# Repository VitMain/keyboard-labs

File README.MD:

# Keyboard Labs

This repository contains the source files for keyboard
designs and keyboard firmware.

# Keyboards

Kicad source files are in `pcb`.

Plotted gerber files can be found under the GitHub repository's
[releases](https://github.com/rgoulter/keyboard-labs/releases/).

| Designation  | Summary/Keywords                                                                       | Image                                                                                                                                                 |
|--------------|----------------------------------------------------------------------------------------|-------------------------------------------------------------------------------------------------------------------------------------------------------|
| [X-1](https://github.com/rgoulter/keyboard-labs#x-1-36-key-split-reversible-pcb-with-weact-studio-mini-f4-dev-board) | 36-key (2x3x5+3), split, column-staggered, MX/choc, sub-100x100, per-key RGB LED, ARM       |                               |
| [X-2](#x-2-5x12-ortholinear-arm-powered-adaptation-of-peejs-lumberjack-pcb)          | 60-key (5x12), un-split, ortholinear, MX/choc, GH60-compatible, "show the components", ARM  |                               |
| [X-2 HSRGB](#x-2-hsrgb-5x12-ortholinear-arm-powered-adaptation-of-peejs-lumberjack-pcb-with-hotswap-and-per-key-rgb)    | 60-key (5x12), un-split, ortholinear, MX/choc, GH60-compatible, "show the components", HotSwap, per-key RGB, ARM  |    |
| [PyKey40 Lite](#pykey40-lite-no-frills-subset-of-the-pykey60-in-bm40jj40-form-factor) | Planck-MIT (4x12, 1x2U), ortholinear, MX, BM40/JJ40-compatible, PCBA, no frills, ARM        |                                                                                                                                                       |
| [PyKey40 HSRGB](#pykey40-hsrgb-4x12-ortholinear-with-hotswap-and-rgb-in-bm40jj40-form-factor) | Planck-MIT (4x12, 1x2U), ortholinear, MX, BM40/JJ40-compatible, PCBA, HotSwap, per-key RGB LED, ARM        |   |
| [Pico42](#pico42-simple-hand-solderable-pcb-in-bm40jj40-form-factor) | 42-key ortholinear, MX/choc, BM40/JJ40-compatible, no frills, ARM        |  |
| [CH552-44](#ch552-44-low-budget-hand-solderable-pcb-in-bm40jj40-form-factor) | 44-key ortholinear, MX, BM40/JJ40-compatible, no frills        |  |
| [CH552-48](#ch552-48-low-budget-pcba-in-bm40jj40-form-factor) | 48-key ortholinear (4x12), MX, BM40/JJ40-compatible, no frills        |  |
| [CH552-48-LPR](#ch552-48-lpr-low-budget-pcba-with-low-profile-redragon-switches) | 48-key ortholinear (4x12), low profile redragon, no frills        |  |
| [CH552-36](#ch552-36-low-budget-36-key-split-keyboard-with-smt-components) | 36-key (2x3x5+3), split, column-staggered, MX, sub-100x100, no frills        |  |
| [WABBLE-60](#wabble-60-5x12-ortholinear-ble-risc-v-powered-adaptation-of-peejs-lumberjack-pcb) | 60-key (5x12), unsplit, ortholinear, MX, GH60-compatible, "show the components", RISC-V        |  |
| [CH32X-48](#ch32x-48-low-budget-pcba-in-bm40jj40-form-factor) | 48-key ortholinear (4x12), MX, BM40/JJ40-compatible, no frills, Risc-V |  |
| [CH32X-36](#ch32x-36-low-budget-36-key-split-keyboard-with-smt-components) | 36-key (2x3x5+3), split, column-staggered, MX, sub-100x100, no frills, RISC-V        |  |
| [CH32X-75-LPR](#ch32x-75-lpr-low-budget-pcba-with-low-profile-redragon-switches) | 75-key ortholinear (5x15), low profile redragon, no frills, RISC-V        |  |

## X-1: 36-key, split, reversible PCB with WeAct Studio Mini F4 dev board

Design goals:

- PCB smaller than 100x100 mm2, so that it's cheaper to fabricate at various PCB
  fabricators.
- Reversible PCB (use the same PCB for left/right halves).
- Using the WeAct Studio MiniF4 "black pill" dev board, a cheap STM32F4 dev
  board that runs ARM.
- Low profile (PCB + choc switches + bumpons).
- Column-staggered arrangement of key switches.
- Fancy features: e.g. per-key RGB LEDs, rotary encoders, OLED screen, DC vibration motors.

Pictures:

_X-1, rev2021.5, MX variation (with rotary encoder, OLED, etc.)._

_X-1, rev2021.5, Choc variation, low-profile (with flipped GD-32 Bluepill devboards)._

_Height comparison between low-profile build (with Choc switches) and with sandwich-case._

_Tented._

_Showing the underside of the PCB through the acrylic bottom layer._

_2D Renders of the PCB, revision rev2021.5_

### Build Guides

- [rev2021.4 Budget Build Guide](docs/buildguide_rev2021.4_budget.md)

- [rev2021.5 Interactive BOM](https://rgoulter.com/keyboard-labs/ibom-keyboard-100x100-minif4-dual-rgb-reversible-rev2021.5.html)

- [rev2021.5 Interactive BOM, No Frills](https://rgoulter.com/keyboard-labs/ibom-x1-minif4_36-rev2021.5-basic.html)

### Keyboard Layout

- Blank Layout at [keyboard-layout-editor.com](http://www.keyboard-layout-editor.com/##@_name=MiniF4%20%22Black%20Pill%22%2036-key%20Split%20Keyboard&notes=PCB%20available%20at%2F:%20https%2F:%2F%2F%2F%2Fgithub.com%2F%2Frgoulter%2F%2Fkeyboard-labs%2F%2F&pcb:true&css=%23keyboard-bg%20%7B%0A%20%20%20%20background-image%2F:%20url(%22https%2F:%2F%2F%2F%2Fraw.githubusercontent.com%2F%2Frgoulter%2F%2Fkeyboard-labs%2F%2Fmaster%2F%2Fdocs%2F%2Fimages%2F%2Fkeyboard-100x100-minif4-dual-rgb-reversible-rev2021.4-ortho-bare-sm.png%22)%2F%3B%0A%7D%3B&@_x:2&a:7%3B&=&_x:5.5%3B&=%3B&@_y:-0.95&x:3%3B&=&_x:3.5%3B&=%3B&@_y:-0.9500000000000001&x:4%3B&=%3B&@_y:-1&x:1%3B&=&_x:4.5%3B&=&_x:2%3B&=%3B&@_y:-0.6000000000000001%3B&=&_x:9.5%3B&=%3B&@_y:-0.5&x:2%3B&=&_x:5.5%3B&=%3B&@_y:-0.95&x:3%3B&=&_x:3.5%3B&=%3B&@_y:-0.9499999999999997&x:1%3B&=&_x:2%3B&=&_x:1.5%3B&=&_x:2%3B&=%3B&@_y:-0.6000000000000001%3B&=&_x:9.5%3B&=%3B&@_y:-0.5&x:2%3B&=&_x:5.5%3B&=%3B&@_y:-0.9500000000000002&x:3%3B&=&_x:3.5%3B&=%3B&@_y:-0.9499999999999997&x:1%3B&=&_x:2%3B&=&_x:1.5%3B&=&_x:2%3B&=%3B&@_y:-0.6000000000000001%3B&=&_x:9.5%3B&=%3B&@_y:-0.4500000000000002&x:2.2%3B&=&_x:5.1000000000000005%3B&=%3B&@_y:-0.5499999999999998&x:3.2%3B&=&_x:3.0999999999999996%3B&=%3B&@_y:-0.5&x:4.2%3B&=&_x:1.0999999999999996%3B&=).

- rgoulter's Layout at <a href="http://www.keyboard-layout-editor.com/##@_backcolor=%23ffffff&name=MiniF4%20%22Black%20Pill%22%2036-key%20Split%20Keyboard,%20rgoulter's%20layout&author=github.com%2F%2Frgoulter%2F%2Fkeyboard-labs&pcb:true%3B&@_x:2&c=%239e9e9e&t=%23000000%0A%23ff0000%0A%2300ff00%0A%230000ff%3B&=.%0AF8%0A*%0A8&_x:5.5&t=%23000000%0A%23ff00ff&f2:1%3B&=C%0AR.HI%3B&@_y:-0.95&x:3&t=%23000000%0A%23ff0000%0A%2300ff00%0A%230000ff&f:3%3B&=P%0AF9%0A(%0A9&_x:3.5&t=%23000000%0A%23ff00ff&f:3%3B&=G%0AR.Tog%3B&@_y:-0.95&x:1&t=%23000000%0A%23ff0000%0A%2300ff00%0A%230000ff&f:3%3B&=,%0AF7%0A%2F&%0A7&_x:2&t=%23000000%0A%0A%2300ff00%0A%230000ff&f:3%3B&=Y%0A%0A%7D%0A%5D&_x:1.5&t=%23000000%0A%23ff00ff&f:3%3B&=F%0AR.Tog&_x:2&f:3%3B&=R%0AR.SI%3B&@_y:-0.6&t=%23000000%0A%23ff0000%0A%2300ff00%0A%230000ff&f:3%3B&=%22%0AF12%0A%7B%0A%5B&_x:9.5&t=%23000000%0A%23ff00ff&f:3%3B&=L%0AR.VI%3B&@_y:-0.5&x:2&t=%23000000%0A%23ff0000%0A%2300ff00%0A%230000ff&f:3%3B&=E%0AF5%0A%25%0A5%0ACtrl&_x:5.5&t=%23000000%0A%23ff00ff%0A%23ffff00%0A%2300ffff&fa@:0&:2&:2&:2&:1%3B%3B&=T%0A%3Ci%20class%2F='kb%20kb-Multimedia-Volume-Up-1'%3E%3C%2F%2Fi%3E%0A%2F&uarr%2F%3B%0A%2F&uarr%2F%3B%0ACtrl%3B&@_y:-0.95&x:3&t=%23000000%0A%23ff0000%0A%2300ff00%0A%230000ff&f:3%3B&=U%0AF6%0A%5E%0A6%0AShift&_x:3.5&t=%23000000%0A%23ff00ff%0A%23ffff00%0A%2300ffff&f:3%3B&=H%0A%3Ci%20class%2F='kb%20kb-Multimedia-Volume-Down-2'%3E%3C%2F%2Fi%3E%0A%2F&darr%2F%3B%0A%2F&darr%2F%3B%0AShift%3B&@_y:-0.95&x:1&t=%23000000%0A%23ff0000%0A%2300ff00%0A%230000ff&f:3%3B&=O%0AF4%0A$%0A4%0AGUI&_x:2&t=%23000000%0A%0A%2300ff00%0A%230000ff&f:3%3B&=I%0A%0A+%0A%2F=&_x:1.5&t=%23000000%0A%23ff00ff%0A%23ffff00%0A%2300ffff&f:3%3B&=D%0A%3Ci%20class%2F='kb%20kb-Multimedia-Rewind-Start'%3E%3C%2F%2Fi%3E%0A%2F&larr%2F%3B%0A%2F&larr%2F%3B&_x:2&f:3%3B&=N%0A%3Ci%20class%2F='kb%20kb-Multimedia-FastForward-End'%3E%3C%2F%2Fi%3E%0A%2F&rarr%2F%3B%0A%2F&rarr%2F%3B%0AGUI%3B&@_y:-0.6000000000000001&t=%23000000%0A%23ff0000%0A%2300ff00%0A%230000ff&f:3%3B&=A%0AF11%0A~%0A%60%0AAlt&_x:9.5&t=%23000000&f:3%3B&=S%0A%0A%0A%0AAlt%3B&@_y:-0.5&x:2&t=%23000000%0A%23ff0000%0A%2300ff00%0A%230000ff&f:3%3B&=J%0AF2%0A%2F@%0A2&_x:5.5&t=%23000000%0A%0A%23ffff00%0A%2300ffff&fa@:0&:2&:0&:1%3B%3B&=W%0A%0A%2F&uArr%2F%3B%0APgup%3B&@_y:-0.9499999999999997&x:3&t=%23000000%0A%23ff0000%0A%2300ff00%0A%230000ff&f:3%3B&=K%0AF3%0A%23%0A3&_x:3.5&t=%23000000%0A%23ff00ff%0A%23ffff00%0A%2300ffff&fa@:0&:1&:0&:1%3B%3B&=M%0ADV.%0A%2F&dArr%2F%3B%0APgdn%3B&@_y:-0.9500000000000002&x:1&t=%23000000%0A%23ff0000%0A%2300ff00%0A%230000ff&f:3%3B&=Q%0AF1%0A!%0A1&_x:2&t=%23000000%0A%0A%2300ff00%0A%230000ff&f:3%3B&=X%0A%0A%3F%0A%5C&_x:1.5&t=%23000000%0A%23ff00ff%0A%23ffff00%0A%2300ffff&f:3%3B&=B%0AQW.%0A%2F&lArr%2F%3B%0AHome&_x:2&t=%23000000%0A%0A%23ffff00%0A%2300ffff&f:3%3B&=V%0A%0A%2F&rArr%2F%3B%0AEnd%3B&@_y:-0.6000000000000001&t=%23000000%0A%23ff0000%0A%2300ff00%0A%230000ff&f:3%3B&=%2F%3B%0AF10%0A%3F%0A%2F%2F&_x:9.5&t=%23000000%0A%0A%0A%2300ffff&f:3%3B&=Z%0A%0A%0AIns%3B&@_y:-0.4500000000000002&x:2.2&t=%23000000%0A%0A%2300ff00%0A%230000ff%0A%23ffff00&f:2%3B&=Tab%0A%0A(%0A.%0AMouse&_x:5.1000000000000005&t=%23000000%0A%23ff00ff%0A%23ffff00%0A%0A%23ff0000%3B&=Del%0A%3Ci%20class%2F='kb%20kb-Multimedia-Mute-1'%3E%3C%2F%2Fi%3E%0AM3%0A%0AFn%3B&@_y:-0.5499999999999998&x:3.2&t=%23000000%0A%0A%2300ff00%0A%230000ff%0A%23ff00ff%3B&=Esc%0A%0A)%0A0%0AMedia&_x:3.1000000000000005&t=%23000000%0A%23ff00ff%0A%23ffff00%0A%0A%2300ff00%3B&=Ent%0A%3Ci%20class%2F='kb%20kb-Multimedia-Stop'%3E%3C%2F%2Fi%3E%0AM2%0A%0ASym%3B&@_y:-0.5&x:4.2&t=%23000000%0A%0A%2300ff00%0A%230000ff%0A%2300ffff%3B&=Spc%0A%0A%2F_%0A-%0ANav&_x:1.1000000000000005&t=%23000000%0A%23ff00ff%0A%23ffff00%0A%0A%230000ff%3B&=Bksp%0A%3Ci%20class%2F='kb%20kb-Multimedia-Play-Pause'%3E%3C%2F%2Fi%3E%0AM1%0A%0ANum">keyboard-layout-editor.com</a>.

### Typing Demonstration Videos

typings.gg:

typing.io:

## X-2: 5x12 Ortholinear, ARM-powered Adaptation of peej's Lumberjack PCB

peej's [lumberjack-keyboard](https://github.com/peej/lumberjack-keyboard) is a cool and creative
design, which continues the style of "show the components" used by keyboards like
the [plaid](https://github.com/hsgw/plaid).

One downside to it is that DIP microcontrollers are relatively weak.
Development boards are a spiritual-successor to DIP microcontrollers,
so I wanted to adapt the striking Lumberjack design to a more
powerful development board.

Design goals:

- Using STM32 dev board. (ARM-powered!).
- Adapt the Lumberjack design.
  - In a "show the components" style.
  - Fits in tray-mount GH60 case.
  - (Relatively) easy to solder.

Pictures:

_X-2 PCB assembled, using a Bluepill devboard, with MX switches, in a cheap GH-60 case._

_X-2 PCB assembled, using a WeAct Studio MiniF4 "Blackpill" devboard, with Choc switches, in a layered acrylic case._

_2D Renders of the PCB, revision rev2021.1_

### Build Guides

- [rev2021.1 Interactive BOM](https://rgoulter.com/keyboard-labs/ibom-keyboard-x2-lumberjack-arm-rev2022.1.html)

## X-2 HSRGB: 5x12 Ortholinear, ARM-powered Adaptation of peej's Lumberjack PCB, with HotSwap and per-key RGB

A fancier version of the X-2 above. With all the benefits of the X-2 (fits in GH-60 case, powerful microcontroller),
but with a RGB lighting, which makes the keyboard a bit fancier.

Design goals:

- Same as X-2:
  - Using STM32 dev board. (ARM-powered!).
  - Adapt the Lumberjack design.
    - In a "show the components" style.
    - Fits in tray-mount GH60 case.
    - (Relatively) easy to solder.
- Additional fancy features:
  - HotSwap: the PCB uses Kailh's MX Hotswap sockets. This allows being able to swap out which switches
    are used by the keyboard, without needing to resolder (or resort to using PCB rivets).
  - RGB lighting: the PCB allows for putting RGB lights under each key, as well as RGB underglow.

Pictures:

_X-2 HSRGB PCB assembled, using a Bluepill devboard, with MX switches, in a cheap GH-60 case. Using MX switches with transparent housing, like Kailh's Jellyfish switches, enhances the RGB lighting._

_X-2 HSRGB PCB assembled, view of the back._

### Build Guides

- [HSRGB, rev2022.1 Interactive BOM](https://rgoulter.com/keyboard-labs/ibom-keyboard-x2-lumberjack-arm-hsrgb-rev2022.1.html)

## PyKey40 Lite: No-Frills Subset of the PyKey60 in BM40/JJ40 Form-Factor

My first PCBA design.

Takes jpconstantineau's [PyKey60](https://github.com/jpconstantineau/PyKey60),
and arranges a no-frills (no RGB, no hotswap, no speaker) subset of it to be a drop in replacement for the BM40/JJ40 PCB.

Design goals:

- As this is my first PCBA design: a simple design that works.

Pictures:

_2D Renders of the PCB, revision rev2023.3_

## PyKey40 HSRGB: 4x12 Ortholinear with HotSwap and RGB in BM40/JJ40 Form-Factor

A 4x12 ortholinear with hotswap sockets, and per-key RGB and underglow, using the RP2040 MCU, with mounts compatible with the JJ40/BM40.

Design goals:

- Fancy features: hotswap sockets, RGB.

- Same mounting holes as JJ40/BM40/PyKey40.

Pictures:

_PyKey40 HSRGB PCB assembled in a high-profile aluminium case._

_2D Renders of the PCB, revision rev2023.1_

## Pico42: Simple Hand-Solderable PCB in BM40/JJ40 Form-Factor

A very simple, hand-solderable PCB which uses the Raspberry Pi Pico dev board.

I made this design because in my first attempt at designing a CNC case for the PyKey40,
I put the cutout for the USB connector in the wrong place.
Having a design which doesn't use a USB connector underneath the PCB works around this.

The form factor encourages the thumbs to use 2-3 keys each (and rely on the pinky fingers less).

Design goals:

- Simple, hand-solderable PCB.

- Uses Raspberry Pi Pico devboard. / Doesn't use USB connector underneath PCB.

- Same mounting holes as JJ40/BM40/PyKey40.

- Same pinout as PyKey40 (PyKey60).

Pictures:

_Pico42 PCB assembled with MX switches, in a low profile aluminium case._

_Height of the Pico mounted on round-pin male headers in female headers._

_Pico42 PCB assembled with Kailh Choc switches, in a sandwich case._

_Underside of the Pico42 in a sandwich style case._

_2D Renders of the PCB, revision rev2023.2_

### Build Guides

- [rev2023.1 Interactive BOM](https://rgoulter.com/keyboard-labs/ibom-keyboard-pico42-rev2023.1.html)

- [rev2023.1 Build Guide Notes](docs/buildguide-keyboard_pico42-rev2023.1.md)

## CH552-44: Low-Budget Hand-Solderable PCB in BM40/JJ40 Form-Factor

A very simple, hand-solderable 44-key PCB which uses the WeAct Studio's CH552
devboard.

The form factor encourages the thumbs to use 2-3 keys each (and rely on the
pinky fingers less).

The keyboard uses semickolon's [fak](https://github.com/semickolon/fak)
firmware, which uses the sophisticated and modern
[Nickel](https://nickel-lang.org/) configuration language to declare keyboard
and keymap definitions.

The CH552 is cheaper than the RP2040, although is much less powerful. e.g.
you're probably not going to get Vial on a CH552 keyboard. In practice, fak
seems well suited for small-keyboard enthusiasts.

Since the CH552 has relatively few GPIO pins, the matrix uses 7 rows of 7
columns (= 14 GPIO pins), rather than a more traditional 4 rows of 12 columns
(which would use 16 GPIO pins).

Design goals:

- Low Budget.

- Simple, hand-solderable PCB.

- Uses [WeAct Studio's CH552 core board](https://www.aliexpress.com/item/1005004141926425.html).

- Same mounting holes as JJ40/BM40/PyKey40.

Pictures:

_CH552-44 (rev2023.1) in a sandwich style case._

_Underside of the CH552-44 (rev2023.1) in a sandwich style case._

_2D Renders of the PCB, revision rev2023.2_

### Build Guides and Release Assets

- [rev2023.2 Interactive BOM](https://rgoulter.com/keyboard-labs/ibom-keyboard-ch552-44-rev2023.2.html)

- [rev2023.2 Build Guide Notes](https://github.com/rgoulter/keyboard-labs/blob/master/docs/buildguide-keyboard_ch552-44-rev2023.2.md)

#### Firmware

- Firmware: See [rgoulter/fak-config](https://github.com/rgoulter/fak-config)

(NOTE: for flashing new firmware, on Windows, [I recommend the official WCHISPTool](https://www.wch-ic.com/downloads/WCHISPTool_Setup_exe.html). For flashing using open-source software, it's much easier to flash firmware onto the CH552 from Linux, e.g. [docs/guide-liveiso-flashing-fak.md](https://github.com/rgoulter/keyboard-labs/blob/master/docs/guide-liveiso-flashing-fak.md)).

#### Plates and Cases

A bottom plate can be used to protect the components underneath the PCB.

Source files for plates to cut (or cases to 3D print) can be found under `cad/` in this repository.

## CH552-48: Low-Budget PCBA in BM40/JJ40 Form-Factor

A very simple 48-key PCBA which uses the CH552 MCU.

The keyboard uses semickolon's [fak](https://github.com/semickolon/fak) firmware, which uses the sophisticated and modern [Nickel](https://nickel-lang.org/) configuration language to declare keyboard and keymap definitions.

The CH552 is cheaper than the RP2040, although is much less powerful. e.g. you're probably not going to get Vial on a CH552 keyboard. In practice, fak seems well suited for small-keyboard enthusiasts.

Since the CH552 has relatively few GPIO pins, the matrix uses 7 rows of 7
columns (= 14 GPIO pins), rather than a more traditional 4 rows of 12 columns
(which would use 16 GPIO pins).

Design goals:

- PCBA and Ortho 4x12 improvement upon the [CH552-44](https://github.com/rgoulter/keyboard-labs#ch552-44-low-budget-hand-solderable-pcb-in-bm40jj40-form-factor).

- Low Budget.

- Use CH552 for the fak firmware.

- Same mounting holes as JJ40/BM40/PyKey40.

Pictures:

_CH552-48 in a sandwich style case._

_Underside of the CH552-48 in a sandwich style case._

_Underside of the CH552-48, showing the PCBA components.._

_2D Renders of the PCB, revision rev2023.1_

#### Firmware

- Firmware: See [rgoulter/fak-config](https://github.com/rgoulter/fak-config)

(NOTE: for flashing new firmware, on Windows, [I recommend the official WCHISPTool](https://www.wch-ic.com/downloads/WCHISPTool_Setup_exe.html). For flashing using open-source software, it's much easier to flash firmware onto the CH552 from Linux, e.g. [docs/guide-liveiso-flashing-fak.md](https://github.com/rgoulter/keyboard-labs/blob/master/docs/guide-liveiso-flashing-fak.md)).

#### Plates and Cases

A bottom plate can be used to protect the components underneath the PCB.

Source files for plates to cut (or cases to 3D print) can be found under `cad/` in this repository.

## CH552-48-LPR: Low-Budget PCBA with Low Profile Redragon Switches

Variation of the CH552-48 which uses Redragon low profile switches.

Redragon low profile switches are significantly cheaper than other low profile switches,
especially the popular Kailh Choc v1 switches.

Height varies depending on keycap profile. The distance between the top of the
PCB and the top of the keycap is around 11mm for Redragon low profile switches
with low profile keycaps.  (In comparison, the same measurement is 10-11mm for
Kailh Choc v1, and about 20mm for MX).

Unlike MX switches (where switches from different manufacturers will have compatible pin positions),
different "low profile" switches have different pin positions from each other.
So, to use Redragon "low profile" switches, you need a PCB designed for Redragon low profile switches.

The KiCad footprint I used for this design can be found under `pcb/` in this repository.

Redragon switches support keycaps with MX stems, unlike Kailh Choc v1.
Albeit, general MX keycap profiles (e.g. XDA) are NOT fully compatible with "low profile" switches,
since the bottom of the keycap bottoms-out below where a switch plate sits.
Instead, "low profile" switches with MX stems need 'slim' keycaps, such as [NuPhy's](https://www.aliexpress.us/item/3256805311515595.html) or [womier's](https://www.aliexpress.com/item/1005004613625285.html), etc.

Since the Redragon low profile switches have 3-pins, it's best to assemble the keyboard using a switch plate
(e.g. a lasercut 1.0mm metal plate). Pictures below show what a build without a plate looks like.

Design goals:

- A keyboard that uses Redragon low profile switches.

Pictures:

_CH552-48-LPR in a JJ40 low profile aluminium case._

_CH552-48-LPR in a sandwich style case._

_Underside of the CH552-48-LPR in a sandwich style case._

_Switches mounted to the PCB without a plate._

_Unsoldered underside of the PCB, with switches mounted in a plate._

_2D Renders of the PCB, revision rev2023.1_

#### Firmware

Same as for the [CH552-48](#ch552-48-low-budget-pcba-in-bm40jj40-form-factor).

- Firmware: See [rgoulter/fak-config](https://github.com/rgoulter/fak-config)

(NOTE: for flashing new firmware, on Windows, [I recommend the official WCHISPTool](https://www.wch-ic.com/downloads/WCHISPTool_Setup_exe.html). For flashing using open-source software, it's much easier to flash firmware onto the CH552 from Linux, e.g. [docs/guide-liveiso-flashing-fak.md](https://github.com/rgoulter/keyboard-labs/blob/master/docs/guide-liveiso-flashing-fak.md)).

#### Plates and Cases

A bottom plate can be used to protect the components underneath the PCB.

Source files for plates to cut can be found under `cad/` in this repository.

## CH552-36: Low-Budget 36-key Split Keyboard with SMT Components

A very simple, 36-key PCB which uses the CH552 MCU.

The design takes inspiration from [TeXitoi's keyseebee](https://github.com/TeXitoi/keyseebee).

The PCB is smaller than 100x100 mm2, so that it's cheaper to fabricate at
various PCB fabricators.

The keyboard uses semickolon's [fak](https://github.com/semickolon/fak)
firmware, which uses the sophisticated and modern
[Nickel](https://nickel-lang.org/) configuration language to declare keyboard
and keymap definitions.

Design goals:

- Low Budget.

- Use CH552 for the fak firmware.

- "Show the components", "just a keyboard" and "only a PCB with SMD components" from the KeySeeBee.

Pictures:

_CH552-36._

_CH552-36, close up of the MCU area._

_CH552-36, tented, with a coiled TRRS cable._

_Bottom of CH552-36._

_2D Renders of the PCB, revision rev2023.1_

### Build Guides and Release Assets

- [rev2023.1 Interactive BOM](https://rgoulter.com/keyboard-labs/ibom-keyboard-ch552-36-rev2023.1.html)

#### Firmware

- Firmware: See [rgoulter/fak-config](https://github.com/rgoulter/fak-config)

(NOTE: for flashing new firmware, on Windows, [I recommend the official WCHISPTool](https://www.wch-ic.com/downloads/WCHISPTool_Setup_exe.html). For flashing using open-source software, it's much easier to flash firmware onto the CH552 from Linux, e.g. [docs/guide-liveiso-flashing-fak.md](https://github.com/rgoulter/keyboard-labs/blob/master/docs/guide-liveiso-flashing-fak.md)).

## WABBLE-60: 5x12 Ortholinear, BLE, RISC-V-powered Adaptation of peej's Lumberjack PCB

A keyboard using the [WeAct BLE core board](https://aliexpress.com/item/1005004784988010.html).

WeAct's BLE core board is significantly cheaper than the more popular
[nice!nano](https://nicekeyboards.com/nice-nano) BLE board.

The PCB design resembles peej's
[lumberjack-keyboard](https://github.com/peej/lumberjack-keyboard), and mounts
into GH-60 compatible cases like the Lumberjack; however, the WeAct BLE core
board uses a much more powerful MCU than the Lumberjack's 8-bit ATMega328P.

The WABBLE-60 PCB includes LiPo charging.

Design goals:

- Using WeAct BLE core board. (BLE! RISC-V-powered!).
- Adapt the Lumberjack design.
  - In a "show the components" style.
  - Fits in tray-mount GH60 case.
  - (Relatively) easy to solder.

Pictures:

_WABBLE-60._

_2D Renders of the PCB, revision rev2024.2_

### Build Guides and Release Assets

- [rev2024.2 Interactive BOM](https://rgoulter.com/keyboard-labs/ibom-keyboard-wabble-60-rev2024.2.html)

- [rev2024.2 Build Guide](docs/buildguide_wabble-60_rev2024.2.md)

#### Firmware

There are few options for keyboard firmware for the WeAct BLE core board;
 and what options there exist are not very mature.

- My own [smart-keymap](https://github.com/rgoulter/smart-keymap) project includes
   firmware for the WABBLE-60.
  - The project like fak and kirei (mentioned below) uses [Nickel](https://nickel-lang.org/)
     for expressive declarative keymaps.
  - The CH58x firmware is lightly-modified from the CH58x EVT,
     leveraging the smart-keymap library for all the "smart keymap" functionality
     such as layers and tap-hold keys.

- There is a [port of QMK to the CH582](https://github.com/O-H-M2/qmk_port_ch582),
  but as far as I'm aware, it's USB-only, and its BLE-implementation is not
  public.
  - [I wrote about my experience writing firmware with this
    port](https://rgoulter.com/blog/posts/programming/2023-12-27-experience-writing-firmware-with-the-ch582-port-of-qmk.html).
  - [I've put the code for the WABBLE-60 in my qmk_port_ch5xx
    fork](https://github.com/rgoulter/qmk_port_ch5xx).

- [Kirei](https://github.com/semickolon/kirei), from the same author as
[fak](https://github.com/semickolon/fak) supports the CH58x.

  - I recorded a video [demonstrating 110 WPM](https://www.youtube.com/watch?v=mc6wTqoDZe8)
    using a BLE connection.
  - Though, at the time of writing, Kirei's BLE implementation is not yet mature.
     I've had trouble using the BLE keyboard on some platforms.

  - Like fak, Kirei's keymaps are declared in [Nickel](https://nickel-lang.org/).
    Kirei's keymap language is more expressive than fak's.
  - [Here's an example of a
     non-trivial keymap written for
     Kirei](https://github.com/rgoulter/kirei/blob/2e2789838f9dd02c558ced4ca06c2f2e88c32219/src/keymap.ncl)
  - [I've put the code for the WABBLE-60 in my kirei fork](https://github.com/rgoulter/kirei).

- Besides these options, [ch32-rs has a work-in-progress HAL for
  CH58x](https://github.com/ch32-rs/ch58x-hal/).  Its examples include [a
  bare-bones BLE
  Peripheral](https://github.com/ch32-rs/ch58x-hal/blob/20eac4fd7d65b2eaa8b4eae40f882724a5710646/examples/ble-peripheral.rs).

- [WCH's EVT](https://github.com/openwch/ch583) has many examples for the CH58x
  (including USB HID Keyboard, USB+BLE, BLE HID, BLE Central+Peripheral, BLE OTA
  IAP).

WeAct also have a BLE core board which uses CH592. However, the CH592 has even
less support than the CH58x.

## CH32X-48: Low-Budget PCBA in BM40/JJ40 Form-Factor

A very simple 48-key PCBA which uses the CH32X MCU.

It's essentially a port of the [CH552-48](#ch552-48-low-budget-pcba-in-bm40jj40-form-factor) for the CH32X MCU.

The keyboard uses rgoulter's [smart-keymap](https://github.com/rgoulter/smart-keymap) firmware,
which uses the sophisticated and modern [Nickel](https://nickel-lang.org/) configuration language to declare keyboard and keymap definitions.

The CH32X MCU is about as cheap as the CH55x MCUs, but is significantly more powerful.
The CH32X MCU uses Risc-V, and supports writing firmware with Rust.

Design goals:

- PCBA, port of the [CH552-48](#ch552-48-low-budget-pcba-in-bm40jj40-form-factor) to the CH32X MCU.

- Low Budget.

- Same mounting holes as JJ40/BM40/PyKey40.

Pictures:

_CH32X-48 in a sandwich style case._

_2D Renders of the PCB, revision rev2025.4_

#### Firmware

- Firmware: See [rgoulter/smart-keymap](https://github.com/rgoulter/smart-keymap)

#### Plates and Cases

A bottom plate can be used to protect the components underneath the PCB.

Source files for plates to cut (or cases to 3D print) can be found under `cad/` in this repository.

## CH32X-36: Low-Budget 36-key Split Keyboard with SMT Components

A very simple, 36-key PCB which uses the CH32X MCU.

It's essentially a port of the [CH552-36](#ch552-36-low-budget-36-key-split-keyboard-with-smt-components) for the CH32X MCU.

The design takes inspiration from [TeXitoi's keyseebee](https://github.com/TeXitoi/keyseebee).

The PCB is smaller than 100x100 mm2, so that it's cheaper to fabricate at
various PCB fabricators.

The keyboard uses rgoulter's [smart-keymap](https://github.com/rgoulter/smart-keymap) firmware,
which uses the sophisticated and modern [Nickel](https://nickel-lang.org/) configuration language to declare keyboard and keymap definitions.

The CH32X MCU is about as cheap as the CH55x MCUs, but is significantly more powerful.
The CH32X MCU uses Risc-V, and supports writing firmware with Rust.

Design goals:

- Low Budget.

- "Show the components", "just a keyboard" and "only a PCB with SMD components" from the KeySeeBee.

Pictures:

_CH32X-36._

_2D Renders of the PCB, revision rev2025.1_

### Build Guides and Release Assets

- [rev2025.1 Interactive BOM](https://rgoulter.com/keyboard-labs/ibom-keyboard-ch32x-36-lhs-rev2025.1.html)

#### Firmware

- Firmware: See [rgoulter/smart-keymap](https://github.com/rgoulter/smart-keymap)

## CH32X-75-LPR: Low-Budget PCBA with Low Profile Redragon Switches

A 5x15 ortholinear keyboard, which uses the CH32X MCU.

The switches are Redragon's low profile switches. See notes under [CH552-48-LPR](#ch552-48-lpr-low-budget-pcba-with-low-profile-redragon-switches).

As with other 5x15 ortholinear keyboards, the CH32X-75-LPR has mounts compatible with many 60% keyboard cases.

The keyboard uses rgoulter's [smart-keymap](https://github.com/rgoulter/smart-keymap) firmware,
which uses the sophisticated and modern [Nickel](https://nickel-lang.org/) configuration language to declare keyboard and keymap definitions.

The LQFP-48 CH32X MCU is significantly cheaper than the LQFP-48 CH55x MCU, and is also significantly more powerful.
The CH32X MCU uses Risc-V, and supports writing firmware with Rust.

The PCB also supports using 0805 SMD LEDs for basic keyboard backlighting.

Design goals:

- A keyboard that uses Redragon low profile switches.

- Fits in a tray-mount GH60 case.

- PCBA.

Pictures:

_CH32X-75-LPR in a GH60 low profile aluminium case._

_2D Renders of the PCB, revision rev2025.1_

#### Firmware

Same as for the [CH32X-48](#ch32x-48-low-budget-pcba-in-bm40jj40-form-factor).

- Firmware: See [rgoulter/smart-keymap](https://github.com/rgoulter/smart-keymap)

# CAD Designs

CAD design files found under `cad/`:

## Tenting Stand

`keyboard_tenting_stand.scad` describes a design which can be laser cut
and assembled to form a adjustable tenting stand. The stand can be adjusted
using an extra wedge piece.

The design accepts various parameters (e.g. width, height, angle, screw diameter).

## Layered Case

An OpenSCAD module which helps for modelling the layers for a layered acrylic case.

## Simple 3D Parameterised Case for CNC/3DP

A set of OpenScad files for a parameterised simple keyboard case design.

I've used outputs from these for CNC milling, as well as for 3D printing.

The case has several parameters, so it should be suitable for a variety of rectangular-shaped PCB keyboards.

_The CNC case, mounting a Pico42._

_The CNC case, top._

_The CNC case, bottom._

_The 3D Printed Pico42 case, mounting a Pico42 with Choc switches, sitting on a laptop's keyboard._

_The 3D Printed Pico42 case, top._

_The 3D Printed Pico42 case, bottom._

_Preview of the case in OpenScad._

# Firmware

Source files under `firmware`.

[QMK](https://qmk.fm/) is the most practical firmware I've used for small
keyboards.  I maintain firmware for my keyboards and my layouts in a [downstream
GitHub
repository](https://github.com/rgoulter/qmk_firmware/tree/rgoulter-keyboards-and-layouts)
on the branch `rgoulter-keyboards-and-layouts`. (This branch will get rebased
onto qmk's `develop` branch from time to time). My code will get synced into the `firmware/qmk` directories.

There is some code for the CircuitPy keyboard firmware
[KMK](https://github.com/KMKfw/kmk_firmware).  (Although, at the time of
writing, KMK doesn't handle home row modifiers well, so IMO it's less suitable for
small keyboards as-is).

There is also keyboard firmware written in Rust using the [keyberon](https://github.com/TeXitoi/keyberon)
firmware under `firmware/keyberon`.

# Scripts

# Kicad PCB to OpenSCAD

My attempt at generating top/bottom plate CAD files *as code*.

The script generates an OpenSCAD file with the `.kicad_pcb` data
(Kicad module positions, board outline as an OpenSCAD module, etc.), which can be used by other OpenSCAD
code.

See: [scripts/README.MD](https://github.com/rgoulter/keyboard-labs/tree/master/scripts#transform-kicad_pcb-to-scad)

_Example output of OpenSCAD code, which makes use of the Kicad PCB data to construct a variety of keyboard plates._

# Notes

- [docs/guide-liveiso-flashing-fak.md](https://github.com/rgoulter/keyboard-labs/blob/master/docs/guide-liveiso-flashing-fak.md):
  guide for using the Live ISO on a bootable USB to flash Fak firmware.

- [docs/pcb-rivets.md](https://github.com/rgoulter/keyboard-labs/blob/master/docs/pcb-rivets.md):
  notes on usage of PCB rivets for allowing hot-swapping switches on
  PCBs with regular footprints.

- [docs/socketing-devboards.md](https://github.com/rgoulter/keyboard-labs/blob/master/docs/socketing-devboards.md):
  some comparison photos of some different ways of socketing
  devboards.

- [docs/rgb-leds-logic-level-shifting.md](https://github.com/rgoulter/keyboard-labs/blob/master/docs/rgb-leds-logic-level-shifting.md):
  some notes on logic level shifting.

- [docs/stm32-flashing-and-bootloaders.md](https://github.com/rgoulter/keyboard-labs/blob/master/docs/stm32-flashing-and-bootloaders.md):
  some notes on bootloaders for STM32.

- [cad/docs/freecad-techdraw-threads.md](https://github.com/rgoulter/keyboard-labs/blob/master/cad/docs/freecad-techdraw-threads.md):
  notes on how to use FreeCad to create a technical drawing to indicate location of threads to be tapped, or where inserts are to be placed.

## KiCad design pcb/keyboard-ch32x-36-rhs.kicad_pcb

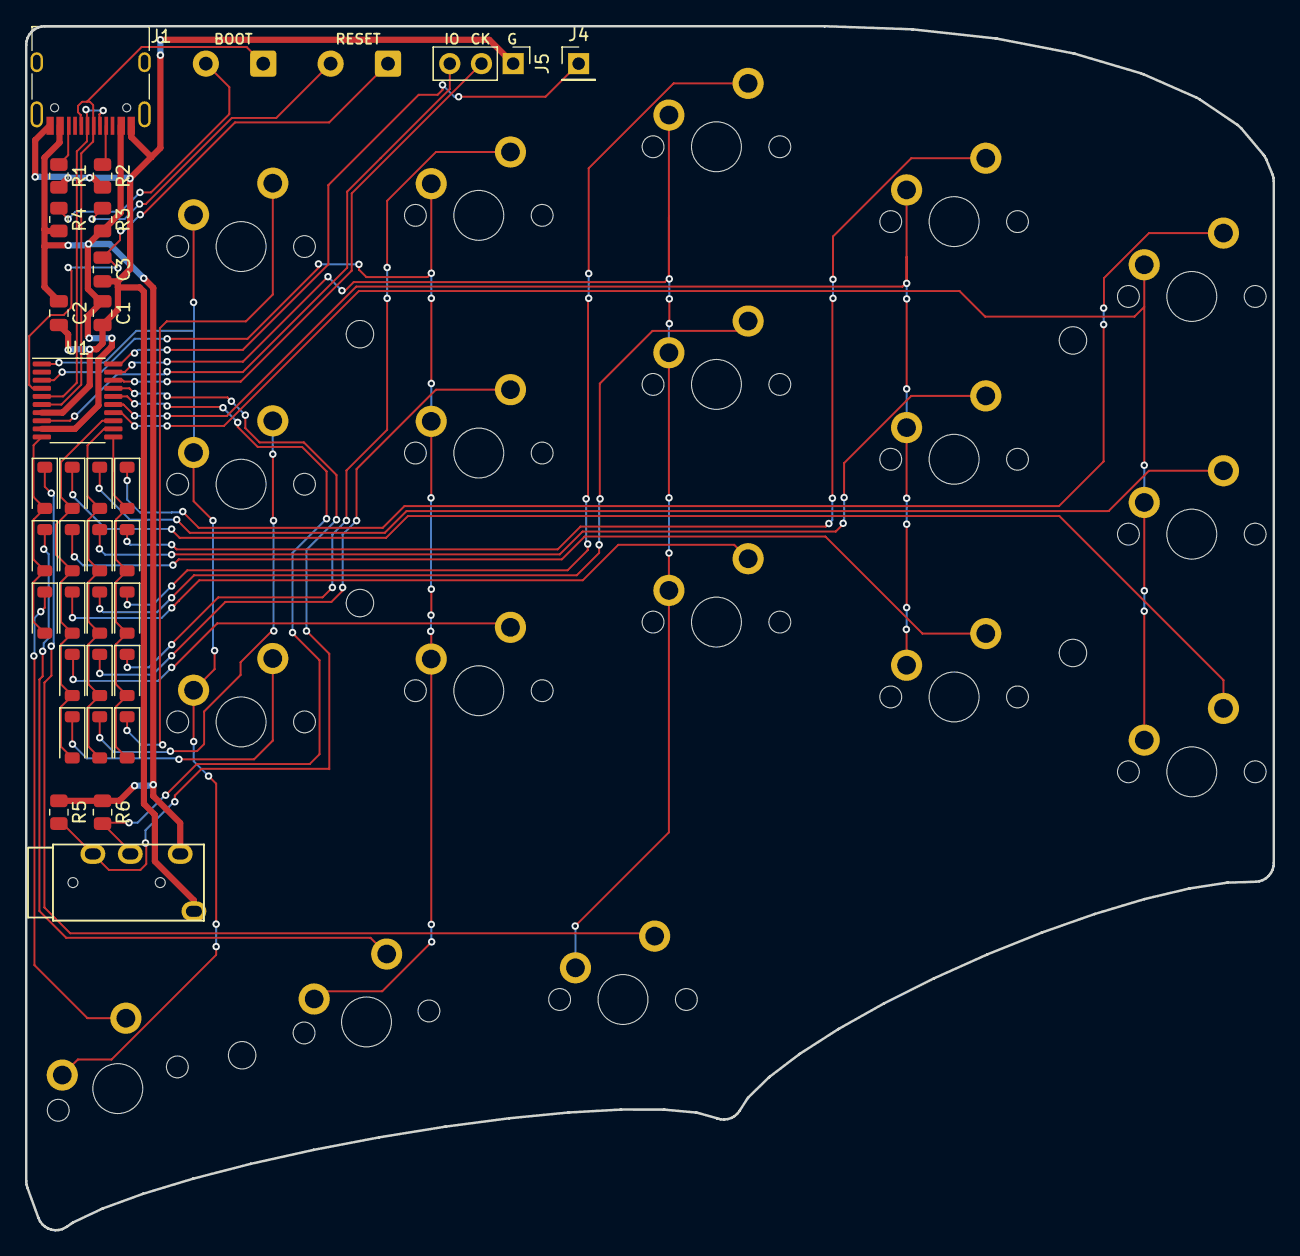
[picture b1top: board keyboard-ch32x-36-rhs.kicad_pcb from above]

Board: 2 copper layers, 100.0 x 96.5 mm, 57 parts (0 on the bottom side), 41 nets.

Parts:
C1, C3: 100n; C_0805_2012Metric
C2: 4.7uF; C_0805_2012Metric
D_1_1, D_1_2, D_1_3, D_1_4, D_1_5, D_2_1, D_2_2, D_2_3, D_2_4, D_2_5, D_3_1, D_3_2, D_3_3, D_3_4, D_3_5, D_4_3, D_4_4, D_4_5: 1N4148; D_SOD-123
H1, H2, H3, H4, H5: M2 mounting hole; MountingHole_2.2mm_M2_DIN965
J1: USB Type-C Receptacle 12-pin; USB_C_Receptacle_HRO_TYPE-C-31-M-12
J2: PJ-320A; TRRS-PJ-320A
J4: Conn_01x02; PinHeader_1x01_P2.54mm_Vertical
J5: Conn_01x03; PinHeader_1x03_P2.54mm_Vertical
R1, R2: 5.1k; R_0805_2012Metric
R3: 330R; R_0805_2012Metric
R4: 10K; R_0805_2012Metric
R5, R6: 2.2k - 10k; R_0805_2012Metric
SW1, SW2: SW_SPST; SolderWire-0.5sqmm_1x02_P4.6mm_D0.9mm_OD2.1mm
SW_1_1, SW_1_2, SW_1_3, SW_1_4, SW_1_5, SW_2_1, SW_2_2, SW_2_3, SW_2_4, SW_2_5, SW_3_1, SW_3_2, SW_3_3, SW_3_4, SW_3_5, SW_4_3, SW_4_4, SW_4_5: MX-compatible; SW_Cherry_MX_PCB_1.00u_BSilkRef
U1: CH32X033F8P6; TSSOP-20_4.4x6.5mm_P0.65mm

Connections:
/5V: C1.1, C2.1, J1.A4 (VBUS), J1.A9 (VBUS), J1.B4 (VBUS), J1.B9 (VBUS), J2.2 (TIP), R3.2, R4.2, R5.1, R6.1, U1.9 (VDD)
/COL1: SW_1_1.1, SW_2_1.1, SW_3_1.1, U1.14 (PA0)
/COL2: SW_1_2.1, SW_2_2.1, SW_3_2.1, U1.15 (PA1)
/COL3: SW_1_3.1, SW_2_3.1, SW_3_3.1, SW_4_3.1, U1.19 (PA4)
/COL4: SW_1_4.1, SW_2_4.1, SW_3_4.1, SW_4_4.1, U1.3 (PB1)
/COL5: SW_1_5.1, SW_2_5.1, SW_3_5.1, SW_4_5.1, U1.1 (PA6)
/DCK: J5.2, U1.18 (DCK)
/DIO: J5.3, U1.8 (DIO)
/DM: J1.A7 (D-), J1.B7 (D-), U1.5 (UDM)
/DOWNLOAD: J1.A6 (D+), J1.B6 (D+), SW2.1 (A), U1.6 (UDP)
/GND: C1.2, C2.2, C3.2, J1.A1 (GND), J1.A12 (GND), J1.B1 (GND), J1.B12 (GND), J2.1 (SLEEVE), J5.1, R1.2, R2.2, U1.7 (GND)
/LHS_RX_RHS_TX: J2.3 (RING1), R6.2, U1.16 (TX2)
/LHS_TX_RHS_RX: J2.4 (RING2), R5.2, U1.17 (RX2)
/RESET: C3.1, SW1.1 (A), U1.4 (RST)
/ROW1: D_1_1.2 (A), D_1_2.2 (A), D_1_3.2 (A), D_1_4.2 (A), D_1_5.2 (A), U1.11 (PA11)
/ROW2: D_2_1.2 (A), D_2_2.2 (A), D_2_3.2 (A), D_2_4.2 (A), D_2_5.2 (A), U1.12 (TX1_)
/ROW3: D_3_1.2 (A), D_3_2.2 (A), D_3_3.2 (A), D_3_4.2 (A), D_3_5.2 (A), U1.13 (PC3)
/ROW4: D_4_3.2 (A), D_4_4.2 (A), D_4_5.2 (A), U1.10 (PA9)
/TX1: J4.1, U1.20 (TX4_1)
unnamed: D_1_1.1 (K), SW_1_1.2
unnamed: D_1_2.1 (K), SW_1_2.2
unnamed: D_1_3.1 (K), SW_1_3.2
unnamed: D_1_4.1 (K), SW_1_4.2
unnamed: D_1_5.1 (K), SW_1_5.2
unnamed: D_2_1.1 (K), SW_2_1.2
unnamed: D_2_2.1 (K), SW_2_2.2
unnamed: D_2_3.1 (K), SW_2_3.2
unnamed: D_2_4.1 (K), SW_2_4.2
unnamed: D_2_5.1 (K), SW_2_5.2
unnamed: D_3_1.1 (K), SW_3_1.2
unnamed: D_3_2.1 (K), SW_3_2.2
unnamed: D_3_3.1 (K), SW_3_3.2
unnamed: D_3_4.1 (K), SW_3_4.2
unnamed: D_3_5.1 (K), SW_3_5.2
unnamed: D_4_3.1 (K), SW_4_3.2
unnamed: D_4_4.1 (K), SW_4_4.2
unnamed: D_4_5.1 (K), SW_4_5.2
unnamed: J1.A5 (CC1), R2.1
unnamed: J1.B5 (CC2), R1.1
unnamed: R3.1, SW1.2 (B)
unnamed: R4.1, SW2.2 (B)

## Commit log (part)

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2022-02-25 add flake.nix and flake.log, with kicad 5 and kicad 6
2022-07-08 kicad: add x-2 hsrgb
2022-07-25 kicad: fix mounting hole
2022-07-25 ignore
2022-07-27 wip; trying to get ibom working again
2023-06-11 cad: x-2: WIP plates to mount to PSD-60 (gasket mount)
2025-01-10 pcb: add CH32X-48 rev2025.1
2025-01-10 pcb: add CH32X033F8P6 symbol
2025-01-10 pcb: ch32x-48: add notes to schematic
2025-01-10 pcb: ch32x-48: rev2025.2
2025-01-16 pcb: ch32x-48 rev2025.3
    rev2025.3:
    - increase trace width to 0.25,
    - fix DRC.
    - add 10K pullup for Row6 (DIO),
    per testing of the rev2025.1 board.
    rev2025.2:
2025-02-04 pcb: add symbol CH32X035C8T6
2025-02-06 scripts: add kicad_helper/ch32x_75
2025-02-06 scripts: kicad_common: pcbnew removed FP_TEXT
2025-02-06 wip: pcb: ch32x-75
2025-03-23 pcb: ch32x-36-lhs: add SilkScr "G" to SWD
2025-03-23 pcb: ch32x-36-rhs: add SilkScr "G" to SWD
2025-03-23 pcb: ch32x-36 rhs: schematic, more useful pin function
2025-03-23 pcb: ch32x-75: add silkscreen to BOOT, RESET, SWD
2025-04-27 pcb: add ch32x-36 LHS
2025-04-27 pcb: add ch32x-36 RHS
2025-04-27 pcb: ch32x-48 rev2025.4
2025-04-27 pcb: add ch32x-75
2025-04-28 docs: images: add CH32X-48
2025-04-28 readme.md: add keyboard CH32X-48
2025-04-28 docs: images: add CH32X-36
2025-04-28 update Interactive BOMs (add CH32X-36 rev2025.1)
2025-04-28 pcb: add generate-ch32x-36-ibom.sh
2025-04-28 readme.md: add keyboard CH32X-36
2025-04-28 docs: images: add CH32X-75-LPR
2025-04-28 readme.md: add keyboard CH32X-75-LPR
2025-04-28 readme.md: ch32x-75-lpr is also risc-v
2025-09-26 cad: log PCB_USB_CONNECTOR_MID_X
2025-09-26 cad: 3dp case: increase margin for USB connector
2025-10-04 flake.nix: checks: remove qmk- packages
2025-10-04 flake.nix: remove devenv shell
2025-10-04 shellcheck: add for .envrc
2025-10-04 flake.nix: remove checks.pcb
2025-10-04 flake.nix: remove treefmt module
2025-10-04 flake.nix: remove offline-iso package
2025-10-04 flake.lock: nix flake update
2025-10-04 envrc: rm use flake .
2025-10-04 nix: python: set pyproject, build-system
2025-10-04 flake.nix: remove qmk-, pcb- packages
2025-10-04 pcb: kibot: remove pcbdraw from config
2025-10-04 pcb: shell.nix: remove recordmydesktop
2025-10-04 nix: disable use of pcbdraw
2025-10-04 nix: kibot: add lxml to propagatedBuildInputs
2025-10-04 nix: kibot: update to v1.8.4
2025-10-04 pcb: kibot: restore pcbdraw outputs
2025-10-04 pcb: pcbdraw: patch for kicad 9, use older mistune
2025-10-04 nix: restore use of pcbdraw in shell.nix, kibot
2025-10-04 nix: pythonPackages: add mistune 2.0.5
2025-10-04 nix: kiauto: update
2025-10-05 nix: pcb: remove recordmydesktop
2025-10-05 flake.nix: restore checks.pcb
2025-10-05 flake.nix: restore pcb, qmk packages
2025-10-05 nix: pcb: add the ch32x pcbs
2025-10-05 flake.nix: check ch32x pcbs build
2025-10-05 pcb: save keyboard-pico42 with kicad9
2025-10-05 pcb: save keyboard-ch32x-36-lhs with kicad9
2025-10-05 pcb: save keyboard-x2-lumberjack-arm-hsrgb with kicad9
2025-10-05 pcb: save keyboard-pykey40-lite with kicad9
2025-10-05 pcb: save keyboard-ch32x-rhs with kicad9
2025-10-05 pcb: save keyboard-ch32x-48 with kicad9
2025-10-05 pcb: save keyboard-100x100-minif4-dual-rgb-reversible with kicad9
2025-10-05 pcb: save keyboard-ch32x-75 with kicad9
2025-10-05 pcb: save keyboard-x2-lumberjack-arm with kicad9
2025-10-05 pcb: save keyboard-pykey40-hsrgb with kicad9
2025-10-05 pcb: more visible layers for keyboard-x2-lumberjack-arm-hsrgb
2025-10-05 pcb: more visible layers for keyboard-ch32x-36-rhs
2025-10-05 pcb: more visible layers for keyboard-pykey40-lite
2025-10-05 pcb: more visible layers for keyboard-x2-lumberjack-arm
2025-10-05 pcb: more visible layers for keyboard-ch32x-36-lhs
2025-10-05 pcb: more visible layers for keyboard-ch32x-48
2025-10-05 pcb: more visible layers for keyboard-pykey40-hsrgb
2025-10-05 pcb: more visible layers for keyboard-ch32x-75
2025-10-05 pcb: more visible layers for keyboard-pico42
2025-10-05 pcb: more visible layers for keyboard-wabble-60
2025-10-05 pcb: save keyboard-wabble-60 with kicad9
2025-10-05 pcb: more visible layers for keyboard-100x100-minif4-dual-rgb-reversible
2025-10-05 pcb: keyboard-ch32x-36-lhs: fix 3D models
2025-10-05 pcb: keyboard-ch32x-48: fix 3D models
2025-10-05 pcb: fix 3D for keyboard-pykey40-hsrgb
2025-10-05 pcb: kicad mod: rm 3D model from SW_Redragon_LowProfile_PCB_1.00u
2025-10-05 pcb: fix 3D for keyboard-ch32x-75
2025-10-05 pcb: keyboard-ch32x-36-rhs: fix 3D models
2025-10-05 pcb: fix 3D for keyboard-wabble-60
2025-11-16 pcb: kicad: CH32X035C8T6: fill in remaining AF
